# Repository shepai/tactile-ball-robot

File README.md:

# tactile-ball-robot
Repo for the development of the tactile ball 

## Installation 
Navigate to the folder path of tactile-ball-robot/ball-gym/ and use the command
```[bash]
pip install -e .
```

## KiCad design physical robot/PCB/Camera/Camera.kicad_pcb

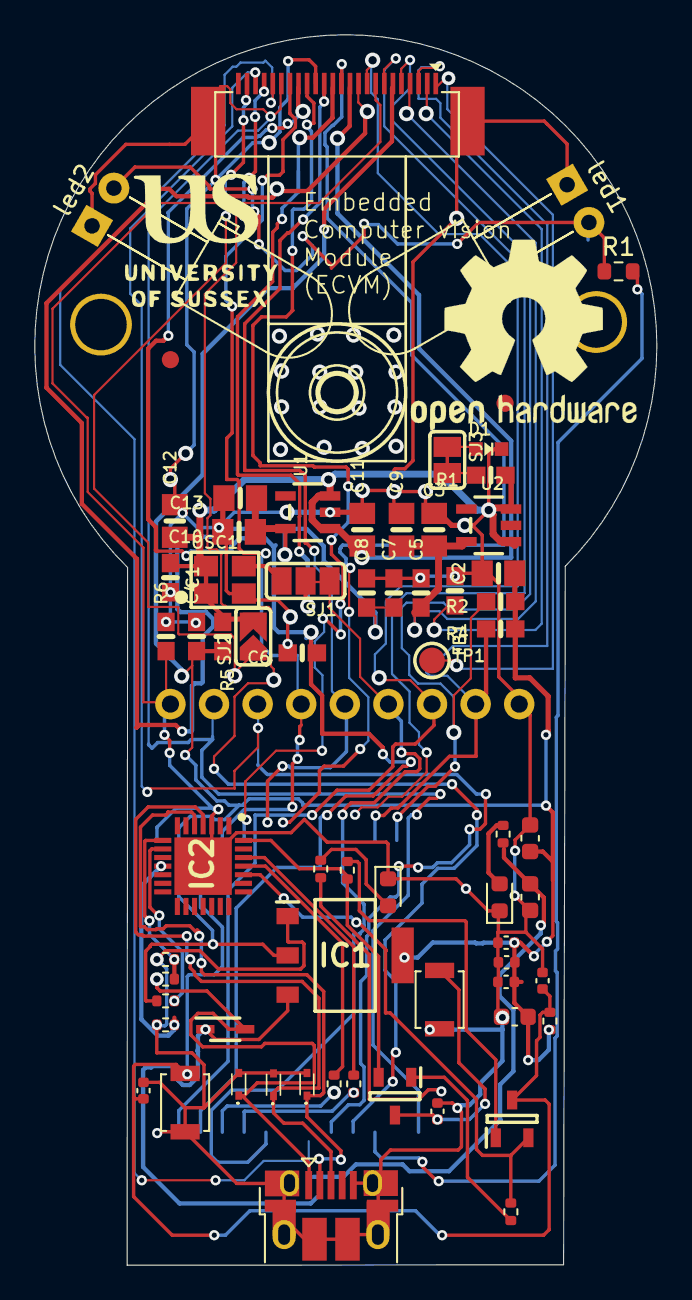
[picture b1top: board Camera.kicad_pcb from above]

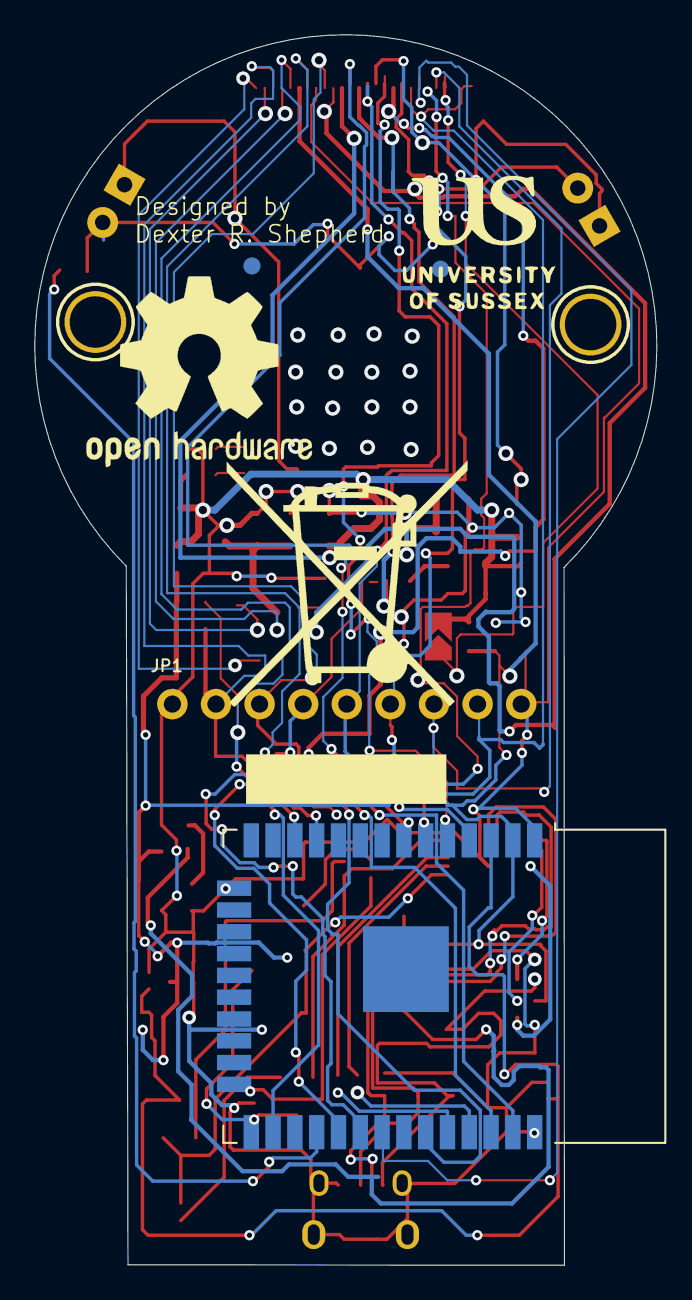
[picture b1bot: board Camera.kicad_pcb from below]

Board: 2 copper layers, 36.2 x 71.7 mm, 96 parts (24 on the bottom side), 36 nets.

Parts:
C1, C7: 22uF/10V(20%); 0603-NO
C2: 22uF/10V(20%); 0805-NO
C3: 4.7uF/6.3V(10%); 0805-NO
C4: 0.1uF/50V(10%)(NC); 0603-NO
C5, C6, C8: 0.1uF/50V(10%); 0603-NO
C9: 0.1uF/50V(10%)(NC); 0805-NO
C10, C11, C12, C13: 10uF; 0805-NO
C14, C15, C20: 22uF/10V(20%); C_0603_1608Metric
C16: 4.7uF/6.3V(10%); C_0402_1005Metric
C17, C22: 0.1uF/50V(10%)(NC); C_0402_1005Metric
C18, C19, C21: 0.1uF/50V(10%); C_0402_1005Metric
D1: LED; CHIPLED_0603_NOOUTLINE
D2: LED_0603_1608Metric
D3: LED; LESD5D50CT1G
D4, D5: LESD5D5.0CT1G; LESD5D50CT1G
D6: LED; SOD2513X120N
D7: LED; LED_0603_1608Metric
FB1: ferrite; 0603-NO
FID1, FID2, FID3, FID4: FIDUCIAL_1MM
IC1: AMS1117-3.3; SOT229P700X180-4N
IC2: CP2102N-A01-GQFN28; QFN50P500X500X80-29N-D
J1: USB_B_Micro; USB_Micro-B_Amphenol_10103594-0001LF_Horizontal
JP1: 1X09_ROUND_70
OSC1: 24MHz 3.3V Oscillator; OSC_3.2X2.5MM
PLABEL0: PLABEL0
PLABEL1: PLABEL1
PLABEL2: PLABEL2
PLABEL3: PLABEL3
PLABEL4: PLABEL4
PLABEL5: PLABEL5
PLABEL8: PLABEL8
PLABEL9: PLABEL9
PLABEL10: PLABEL10
PLABEL11: PLABEL11
PLABEL12: PLABEL12
PLABEL13: PLABEL13
PLABEL14: PLABEL14
PLABEL15: PLABEL15
PLABEL16: PLABEL16
PLABEL17: PLABEL17
PLABEL18: PLABEL18
PLABEL19: PLABEL19
PLABEL20: PLABEL20
PLABEL21: PLABEL21
PLABEL22: PLABEL22
PLABEL23: PLABEL23
PLABEL24: PLABEL24
PLABEL25: PLABEL25
Q1, Q2: SS8050-G; SOT95P240X115-3N
R1: R_0603_1608Metric
R1#2, R2: R; 0603-NO
R3: R; R_0402_1005Metric
R4, R5: 10k(5%); 0603-NO
R6: 0R(5%); 0603-NO
R7, R13, R15: 10k(5%)(NC); R_0402_1005Metric
R8: 0R(5%); R_0402_1005Metric
R9, R12, R14, R16: 2k(5%); R_0402_1005Metric
R10: 22.1K(5%); R_0402_1005Metric
R11: 47.5k(5%); R_0402_1005Metric
SJ1: SOLDERJUMPER_2WAY_OPEN_NOPASTE
SJ2: SOLDERJUMPER_ARROW_NOPASTE
SJ3: SOLDERJUMPER_CLOSEDWIRE
SW1, SW2: SW_Push; SW_SPST_B3U-1000P
TP1: TESTPOINT_ROUND_1.5MM
U1: ESP32-WROOM-32; SOT23-5
U2: OV5640; SOT23-5
U3: ESP32-WROOM-32
U$1, U$17: MOUNTINGHOLE3.0THIN; MOUNTINGHOLE_3.0_PLATEDTHIN
X1: CAMERA_OV2640; OV2640FSL
led1, led2: LED_D5.0mm_Horizontal_O6.35mm_Z15.0mm

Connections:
1.5V: C10.1, C13.1, X1.10
3.3V: C11.1, C12.1, OSC1.1, OSC1.4, SJ2.2, X1.11
+5V: C1.1, C14.1, IC1.3, R9.2
/DTR: IC2.28, Q2.2, R4.2
/EN: C6.1, C9.2, C19.1, C22.2, Q1.3, R7.1, SW2.2, U1.3 (EN), U3.3
/IO0: C4.2, C17.2, Q2.3, SW1.2, U3.25
/IO2: R16.2, U3.24
/RTS: IC2.24, Q1.2, R5.2
/RXD: IC2.25, R6.1
/RXD0: R8.2, U3.34
/TXD: IC2.26, R8.1
/TXD0: R6.2, U3.35
/USB_DN: IC2.5, J1.2 (D-)
/USB_DP: D4.1, IC2.4, J1.3 (D+)
/VBUS: D5.1, J1.1 (VBUS), R10.1
/VDD33: C2.1, C3.1, C5.1, C7.1, C8.1, C15.1, C16.1, C18.1, C20.1, C21.1, IC1.2, IC1.4, IC2.6, IC2.7, R7.2, R12.1, U3.2
AGND: FB1.2, X1.2
DATA1: SJ2.1, X1.23
DATA2: JP1.8, X1.19
DATA4: JP1.7, X1.22
DATA6: JP1.6, X1.18
DATA8: JP1.5, X1.14
EXT_XCLK: JP1.4, SJ1.1
GND: C1.2, C2.2, C3.2, C4.1, C5.2, C6.2, C7.2, C8.2, C9.1, C10.2, C11.2, C12.2, C13.2, C14.2, C15.2, C16.2, C17.1, C18.2, C19.2, C20.2, C21.2, C22.1, D2.1, D3.1 (K), D4.2, D5.2, D6.1 (K), D7.1, FB1.1, IC1.1, IC2.3, IC2.29, J1.5 (GND), J1.6 (Shield), JP1.1, OSC1.2, R11.1, R13.1, R15.1, SW1.1, SW2.1, U1.1 (GND), U2.1 (GND), U3.1, U3.15, U3.38, U3.39, X1.15, X1.SPRT1, X1.SPRT2
HSYNC: JP1.3, X1.9
INT_XCLK: OSC1.3, SJ1.3
unnamed: D3.2 (A), R3.2
unnamed: D6.2 (A), R14.1
unnamed: D7.2, R16.1
unnamed: IC2.11, R15.2
unnamed: R10.2, R11.2
unnamed: U1.2 (VDD), U2.2 (3V)
PWDN: JP1.9, X1.8
SDA: JP1.2, X1.3
STROBE: TP1.P$1, X1.1
XCLK: SJ1.2, X1.13

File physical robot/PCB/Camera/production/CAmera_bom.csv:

Designator,Footprint,Quantity,Value,LCSC Part #
"C1, C7",0603-NO,2,22uF/10V(20%),
"C10, C11, C12, C13",0805-NO,4,10uF,
"C14, C15, C20",0603,3,22uF/10V(20%),
C16,0402,1,4.7uF/6.3V(10%),
"C17, C22",0402,2,0.1uF/50V(10%)(NC),
"C18, C19, C21",0402,3,0.1uF/50V(10%),
C2,0805-NO,1,22uF/10V(20%),
C3,0805-NO,1,4.7uF/6.3V(10%),
C4,0603-NO,1,0.1uF/50V(10%)(NC),
"C5, C6, C8",0603-NO,3,0.1uF/50V(10%),
C9,0805-NO,1,0.1uF/50V(10%)(NC),
D1,CHIPLED_0603_NOOUTLINE,1,LED,
D2,0603,1,,
D3,LESD5D50CT1G,1,LED,
"D4, D5",LESD5D50CT1G,2,LESD5D5.0CT1G,
D6,SOD2513X120N,1,LED,
D7,0603,1,LED,
FB1,0603-NO,1,ferrite,
"FID1, FID2, FID3, FID4",FIDUCIAL_1MM,4,FIDUCIAL_1MM,
IC1,SOT229P700X180-4N,1,AMS1117-3.3,
IC2,QFN50P500X500X80-29N-D,1,CP2102N-A01-GQFN28,
J1,USB_Micro-B_Amphenol_10103594-0001LF_Horizontal,1,USB_B_Micro,
JP1,1X09_ROUND_70,1,,
"LED1, LED2",LED_D5.0mm_Horizontal_O6.35mm_Z15.0mm,2,LED_D5.0mm_Horizontal_O6.35mm_Z15.0mm,
OSC1,OSC_3.2X2.5MM,1,24MHz 3.3V Oscillator,
PLABEL0,PLABEL0,1,,
PLABEL1,PLABEL1,1,,
PLABEL10,PLABEL10,1,,
PLABEL11,PLABEL11,1,,
PLABEL12,PLABEL12,1,,
PLABEL13,PLABEL13,1,,
PLABEL14,PLABEL14,1,,
PLABEL15,PLABEL15,1,,
PLABEL16,PLABEL16,1,,
PLABEL17,PLABEL17,1,,
PLABEL18,PLABEL18,1,,
PLABEL19,PLABEL19,1,,
PLABEL2,PLABEL2,1,,
PLABEL20,PLABEL20,1,,
PLABEL21,PLABEL21,1,,
PLABEL22,PLABEL22,1,,
PLABEL23,PLABEL23,1,,
PLABEL24,PLABEL24,1,,
PLABEL25,PLABEL25,1,,
PLABEL3,PLABEL3,1,,
PLABEL4,PLABEL4,1,,
PLABEL5,PLABEL5,1,,
PLABEL8,PLABEL8,1,,
PLABEL9,PLABEL9,1,,
"Q1, Q2",SOT95P240X115-3N,2,SS8050-G,
R1_2,0603,1,R_0603_1608Metric,
"R1, R2",0603-NO,2,R,
R10,0402,1,22.1K(5%),
R11,0402,1,47.5k(5%),
"R12, R14, R16, R9",0402,4,2k(5%),
"R13, R15, R7",0402,3,10k(5%)(NC),
R3,0402,1,R,
"R4, R5",0603-NO,2,10k(5%),
R6,0603-NO,1,0R(5%),
R8,0402,1,0R(5%),
SJ1,SOLDERJUMPER_2WAY_OPEN_NOPASTE,1,,
SJ2,SOLDERJUMPER_ARROW_NOPASTE,1,,
SJ3,SOLDERJUMPER_CLOSEDWIRE,1,,
"SW1, SW2",SW_SPST_B3U-1000P,2,SW_Push,
TP1,TESTPOINT_ROUND_1.5MM,1,,
"U$1, U$17",MOUNTINGHOLE_3.0_PLATEDTHIN,2,MOUNTINGHOLE3.0THIN,
U1,SOT23-5,1,ESP32-WROOM-32,
U2,SOT23-5,1,OV5640,
U3,ESP32-WROOM-32,1,ESP32-WROOM-32,
X1,OV2640FSL,1,CAMERA_OV2640,
